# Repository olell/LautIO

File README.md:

# LautIO
Mobile PA-System solution

## Hardware Features

- [x] ESP32 (WiFi + Bluetooth)
- [x] ADAU1701 Digital Signal Processor
- [x] 12V, 5V & 3.3V Power Supply from Battery
- [x] 2x TPA3255-Q1 Amplifier (615W each -> 1260W Amp Power)
- [x] USB Ports to charge mobile phones, etc.
- [x] SD Card socket

## Fancy Rendering

## Third party resources
This git repository contains links or files of the following projects:
* `Bootstrap 5` released under the MIT license. (c) 2021 Twitter
* `Bootswach` released under the MIT license. (c) 2021 Thomas Park
* `jQuery 3.6.0` released under the MIT license. (c) 2021 OpenJS Foundation
* `PlatformIO` released under the Apache 2.0 license. (c) 2021 PlatformIO
* `ESPAsyncTCP` released under the GNU LGPL license. (c) 2021 https://github.com/me-no-dev
* `ESPAsyncWebServer` released under the GNU LGPL license. (c) 2021 https://github.com/me-no-dev
* `SigmaDSP library` released under the GNU LGPL license. (c) 2021 https://github.com/MCUdude
* `ArduinoJson library` released under the MIT license. (c) 2021 Benoît Blanchon

## License
MIT License

Copyright (c) 2021 olel

Permission is hereby granted, free of charge, to any person obtaining a copy
of this software and associated documentation files (the "Software"), to deal
in the Software without restriction, including without limitation the rights
to use, copy, modify, merge, publish, distribute, sublicense, and/or sell
copies of the Software, and to permit persons to whom the Software is
furnished to do so, subject to the following conditions:

The above copyright notice and this permission notice shall be included in all
copies or substantial portions of the Software.

THE SOFTWARE IS PROVIDED "AS IS", WITHOUT WARRANTY OF ANY KIND, EXPRESS OR
IMPLIED, INCLUDING BUT NOT LIMITED TO THE WARRANTIES OF MERCHANTABILITY,
FITNESS FOR A PARTICULAR PURPOSE AND NONINFRINGEMENT. IN NO EVENT SHALL THE
AUTHORS OR COPYRIGHT HOLDERS BE LIABLE FOR ANY CLAIM, DAMAGES OR OTHER
LIABILITY, WHETHER IN AN ACTION OF CONTRACT, TORT OR OTHERWISE, ARISING FROM,
OUT OF OR IN CONNECTION WITH THE SOFTWARE OR THE USE OR OTHER DEALINGS IN THE
SOFTWARE.

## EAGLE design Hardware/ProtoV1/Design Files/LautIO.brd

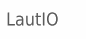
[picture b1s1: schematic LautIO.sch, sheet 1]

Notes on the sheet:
LautIO

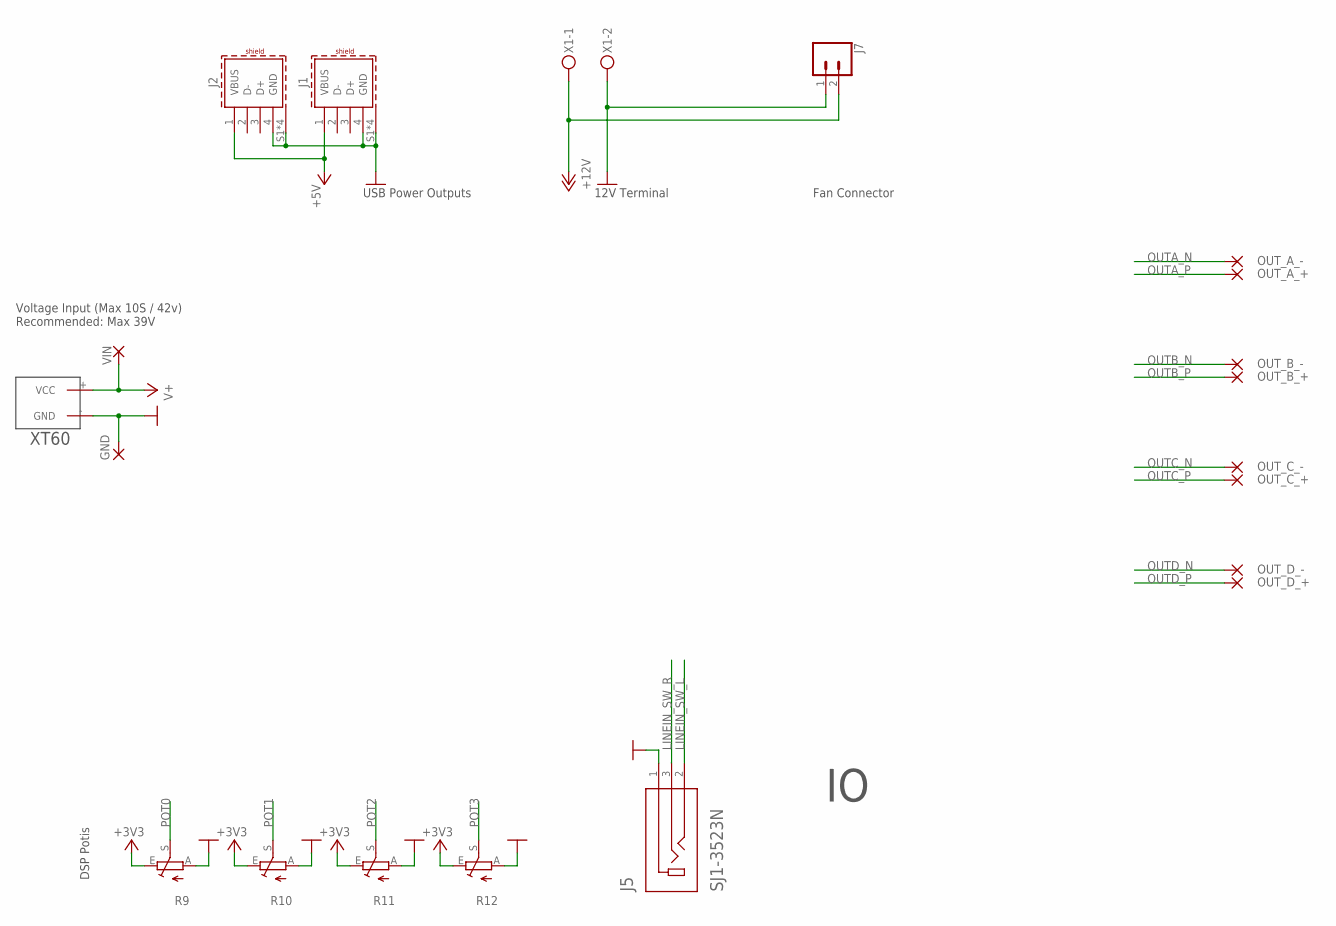
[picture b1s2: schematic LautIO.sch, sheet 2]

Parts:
GND: SMD5; SMD2,54-5,08
J1, J2: 614004134726
J5: SJ1-3523N; CUI_SJ1-3523N
J7: CONN_02; 1X02
OUT_A_+: SMD2; SMD1,27-2,54
OUT_A_-: SMD2; SMD1,27-2,54
OUT_B_+: SMD2; SMD1,27-2,54
OUT_B_-: SMD2; SMD1,27-2,54
OUT_C_+: SMD2; SMD1,27-2,54
OUT_C_-: SMD2; SMD1,27-2,54
OUT_D_+: SMD2; SMD1,27-2,54
OUT_D_-: SMD2; SMD1,27-2,54
R9, R10, R11, R12: TRIM_EU-CIP20C-6MM; CIP20C-6MM
U$1: XT60
VIN: SMD5; SMD2,54-5,08
X1: MKDSN1,5/2-5,08

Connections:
+3V3: R9.E, R10.E, R11.E, R12.E; also elsewhere on the board
+5V: J1.1 (VBUS), J2.1 (VBUS); also elsewhere on the board
+12V: J7.2, X1.1; also elsewhere on the board
GND: GND.1, J1.4 (GND), J1.S1 (SHIELD), J1.S2 (SHIELD), J1.S3 (SHIELD), J1.S4 (SHIELD), J2.4 (GND), J2.S1 (SHIELD), J2.S2 (SHIELD), J2.S3 (SHIELD), J2.S4 (SHIELD), J5.1, J7.1, R9.A, R10.A, R11.A, R12.A, U$1.- (GND), X1.2; also elsewhere on the board
LINEIN_SW_L: J5.2; also elsewhere on the board
LINEIN_SW_R: J5.3; also elsewhere on the board
OUTA_N: OUT_A_-.1; also elsewhere on the board
OUTA_P: OUT_A_+.1; also elsewhere on the board
OUTB_N: OUT_B_-.1; also elsewhere on the board
OUTB_P: OUT_B_+.1; also elsewhere on the board
OUTC_N: OUT_C_-.1; also elsewhere on the board
OUTC_P: OUT_C_+.1; also elsewhere on the board
OUTD_N: OUT_D_-.1; also elsewhere on the board
OUTD_P: OUT_D_+.1; also elsewhere on the board
POT0: R9.S; also elsewhere on the board
POT1: R10.S; also elsewhere on the board
POT2: R11.S; also elsewhere on the board
POT3: R12.S; also elsewhere on the board
V+: U$1.+ (VCC), VIN.1; also elsewhere on the board

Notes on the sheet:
USB Power Outputs
Voltage Input (Max 10S / 42v) Recommended: Max 39V
12V Terminal
DSP Potis
Fan Connector

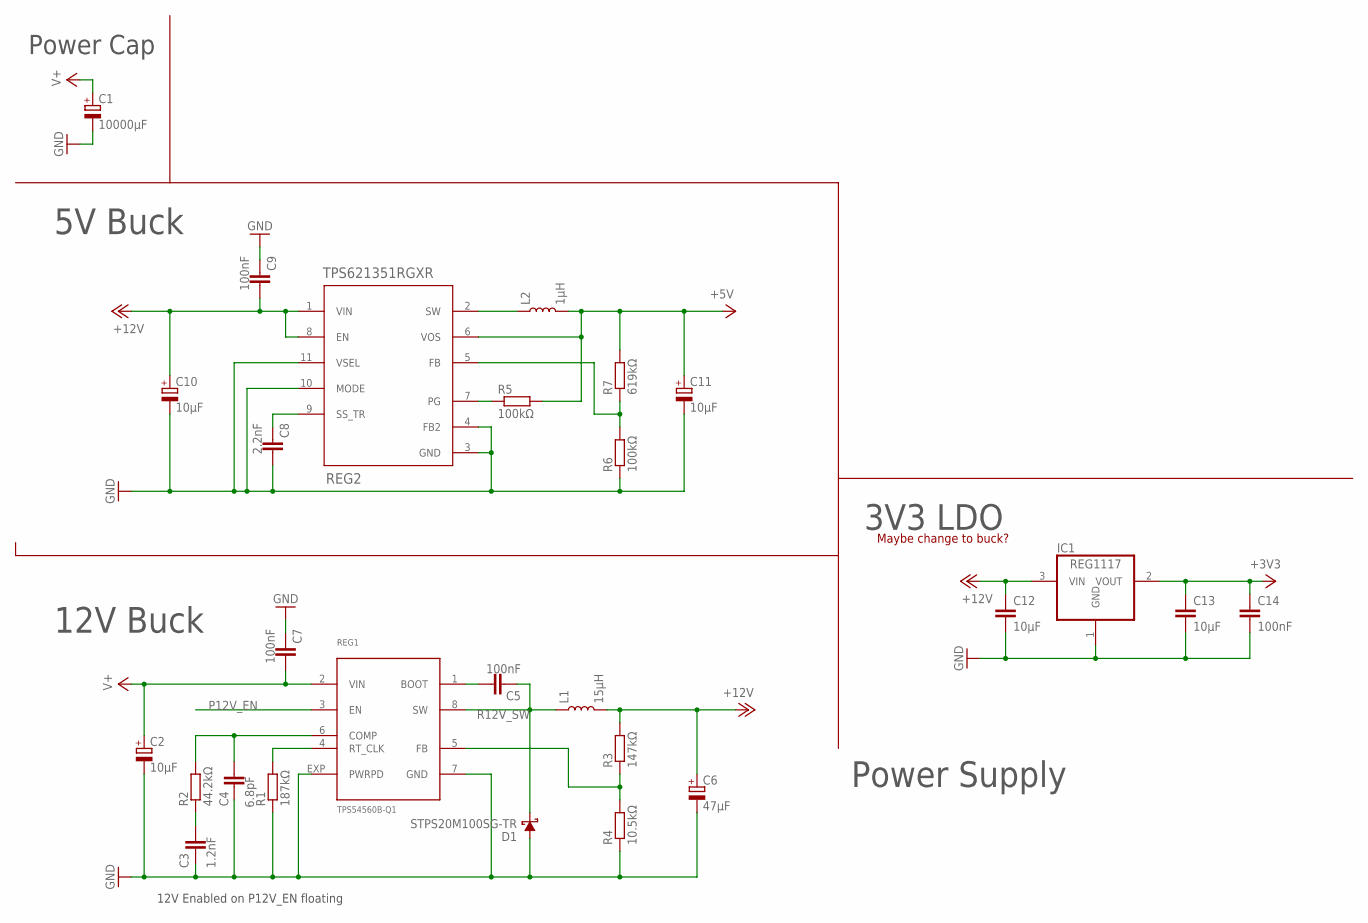
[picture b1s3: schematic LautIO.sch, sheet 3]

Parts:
C1: 10000µF; EB35D
C2, C10, C11: 10µF; 153CLV-0605
C3: 1.2nF; C0603
C4: 6.8pF; C0603
C5, C7, C9, C14: 100nF; C0603
C6: 47µF; 153CLV-0807
C8: 2.2nF; C0603
C12, C13: 10µF; C1206
D1: STPS20M100SG-TR; TO-263/D2PAK
IC1: REG1117; SOT223
L1: 15µH; INDUCTOR_SDR1307
L2: 1µH; INDUCTOR_4X4MM
R1: 187kΩ; R0603
R2: 44.2kΩ; R0603
R3: 147kΩ; R0603
R4: 10.5kΩ; R0603
R5, R6: 100kΩ; R0603
R7: 619kΩ; R0603
REG1: TPS54560B-Q1; HSOP8
REG2: TPS621351RGXR; RGX0011A

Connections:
+3V3: C13.1, C14.1, IC1.2 (VOUT); also elsewhere on the board
+5V: C11.+, L2.P$2 (2), R5.2, R7.2, REG2.6 (VOS); also elsewhere on the board
+12V: C6.+, C9.1, C10.+, C12.1, IC1.3 (VIN), L1.P$2 (2), R3.2, REG2.1 (VIN), REG2.8 (EN); also elsewhere on the board
GND: C1.-, C2.-, C3.2, C4.2, C6.-, C7.2, C8.1, C9.2, C10.-, C11.-, C12.2, C13.2, C14.2, D1.1 (A), D1.3 (A), IC1.1 (GND), R1.1, R4.1, R6.1, REG1.7 (GND), REG1.EXP (PWRPD), REG2.3 (GND), REG2.4 (FB2), REG2.10 (MODE), REG2.11 (VSEL); also elsewhere on the board
unnamed: R1.2, REG1.4 (RT_CLK)
unnamed: C4.1, R2.2, REG1.6 (COMP)
unnamed: C3.1, R2.1
unnamed: C5.1, REG1.1 (BOOT)
unnamed: R6.2, R7.1, REG2.5 (FB)
unnamed: R3.1, R4.2, REG1.5 (FB)
unnamed: L2.P$1 (1), REG2.2 (SW)
unnamed: R5.1, REG2.7 (PG)
unnamed: C8.2, REG2.9 (SS_TR)
P12V_EN: REG1.3 (EN)
R12V_SW: C5.2, D1.2 (C), L1.P$1 (1), REG1.8 (SW)
V+: C1.+, C2.+, C7.1, REG1.2 (VIN); also elsewhere on the board

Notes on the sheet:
Power Supply
Power Cap
12V Enabled on P12V_EN floating
12V Buck
5V Buck
3V3 LDO
Maybe change to buck?

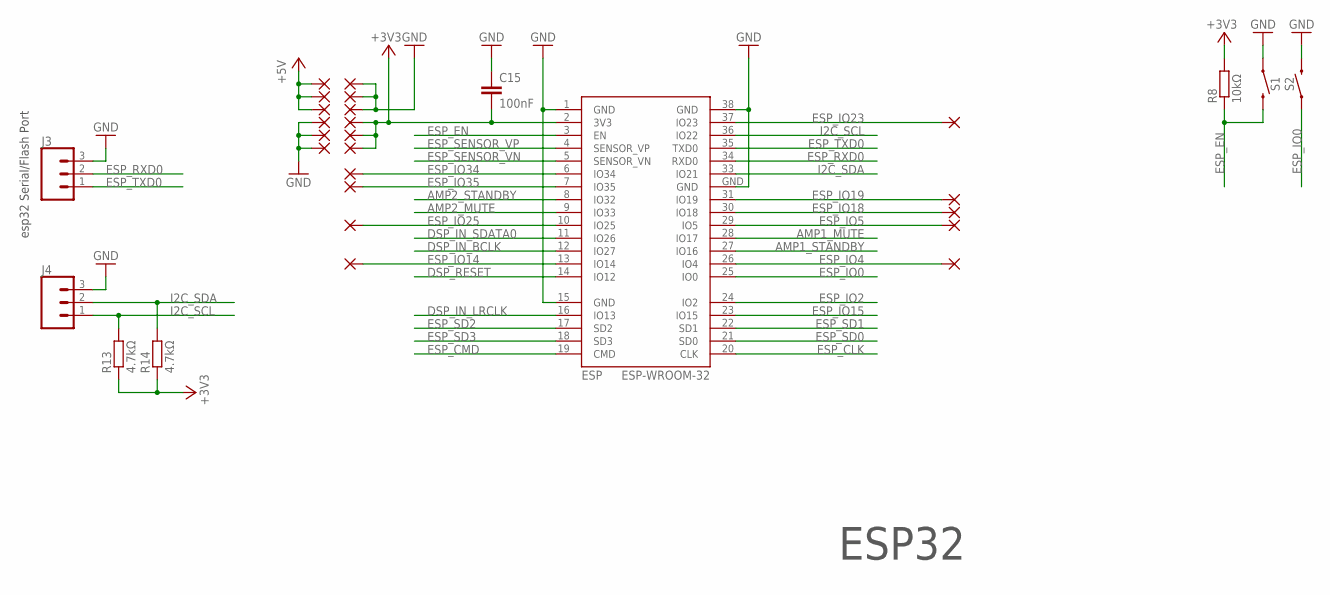
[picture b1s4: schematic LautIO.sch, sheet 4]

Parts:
C15: 100nF; C0603
ESP: ESP-WROOM-32
IO4, IO5, IO14, IO18, IO19, IO23, IO25, IO34, IO35: SMD2; SMD1,27-2,54
J3, J4: 455-1750-1-ND; 1X03
PAD1, PAD2, PAD3, PAD4, PAD5, PAD6, PAD7, PAD8, PAD9, PAD10, PAD11, PAD12: SMD2; SMD1,27-2,54
R8: 10kΩ; R0603
R13, R14: 4.7kΩ; R0603
S1, S2: MOMENTARY-SWITCH-SPST-SMD-6.2MM-TALL; TACTILE_SWITCH_SMD_6.2MM_TALL

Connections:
+3V3: C15.2, ESP.2 (3V3), PAD2.1, PAD4.1, PAD10.1, R8.2, R13.1, R14.1; also elsewhere on the board
+5V: PAD5.1, PAD6.1, PAD7.1; also elsewhere on the board
AMP1_MUTE: ESP.28 (IO17); also elsewhere on the board
AMP1_STANDBY: ESP.27 (IO16); also elsewhere on the board
AMP2_MUTE: ESP.9 (IO33); also elsewhere on the board
AMP2_STANDBY: ESP.8 (IO32); also elsewhere on the board
DSP_IN_BCLK: ESP.12 (IO27); also elsewhere on the board
DSP_IN_LRCLK: ESP.16 (IO13); also elsewhere on the board
DSP_IN_SDATA0: ESP.11 (IO26); also elsewhere on the board
DSP_RESET: ESP.14 (IO12); also elsewhere on the board
ESP_CLK: ESP.20 (CLK)
ESP_CMD: ESP.19 (CMD)
ESP_EN: ESP.3 (EN), R8.1, S1.B2 (2)
ESP_IO0: ESP.25 (IO0), S2.A2 (1)
ESP_IO2: ESP.24 (IO2)
ESP_IO4: ESP.26 (IO4), IO4.1
ESP_IO5: ESP.29 (IO5), IO5.1
ESP_IO14: ESP.13 (IO14), IO14.1
ESP_IO15: ESP.23 (IO15)
ESP_IO18: ESP.30 (IO18), IO18.1
ESP_IO19: ESP.31 (IO19), IO19.1
ESP_IO23: ESP.37 (IO23), IO23.1
ESP_IO25: ESP.10 (IO25), IO25.1
ESP_IO34: ESP.6 (IO34), IO34.1
ESP_IO35: ESP.7 (IO35), IO35.1
ESP_RXD0: ESP.34 (RXD0), J3.2
ESP_SD0: ESP.21 (SD0)
ESP_SD1: ESP.22 (SD1)
ESP_SD2: ESP.17 (SD2)
ESP_SD3: ESP.18 (SD3)
ESP_SENSOR_VN: ESP.5 (SENSOR_VN)
ESP_SENSOR_VP: ESP.4 (SENSOR_VP)
ESP_TXD0: ESP.35 (TXD0), J3.1
GND: C15.1, ESP.1 (GND), ESP.15 (GND), ESP.38 (GND), ESP.GND, J3.3, J4.3, PAD1.1, PAD3.1, PAD8.1, PAD9.1, PAD11.1, PAD12.1, S1.A2 (1), S2.B2 (2); also elsewhere on the board
I2C_SCL: ESP.36 (IO22), J4.1, R13.2; also elsewhere on the board
I2C_SDA: ESP.33 (IO21), J4.2, R14.2; also elsewhere on the board

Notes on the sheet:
ESP32
esp32 Serial/Flash Port

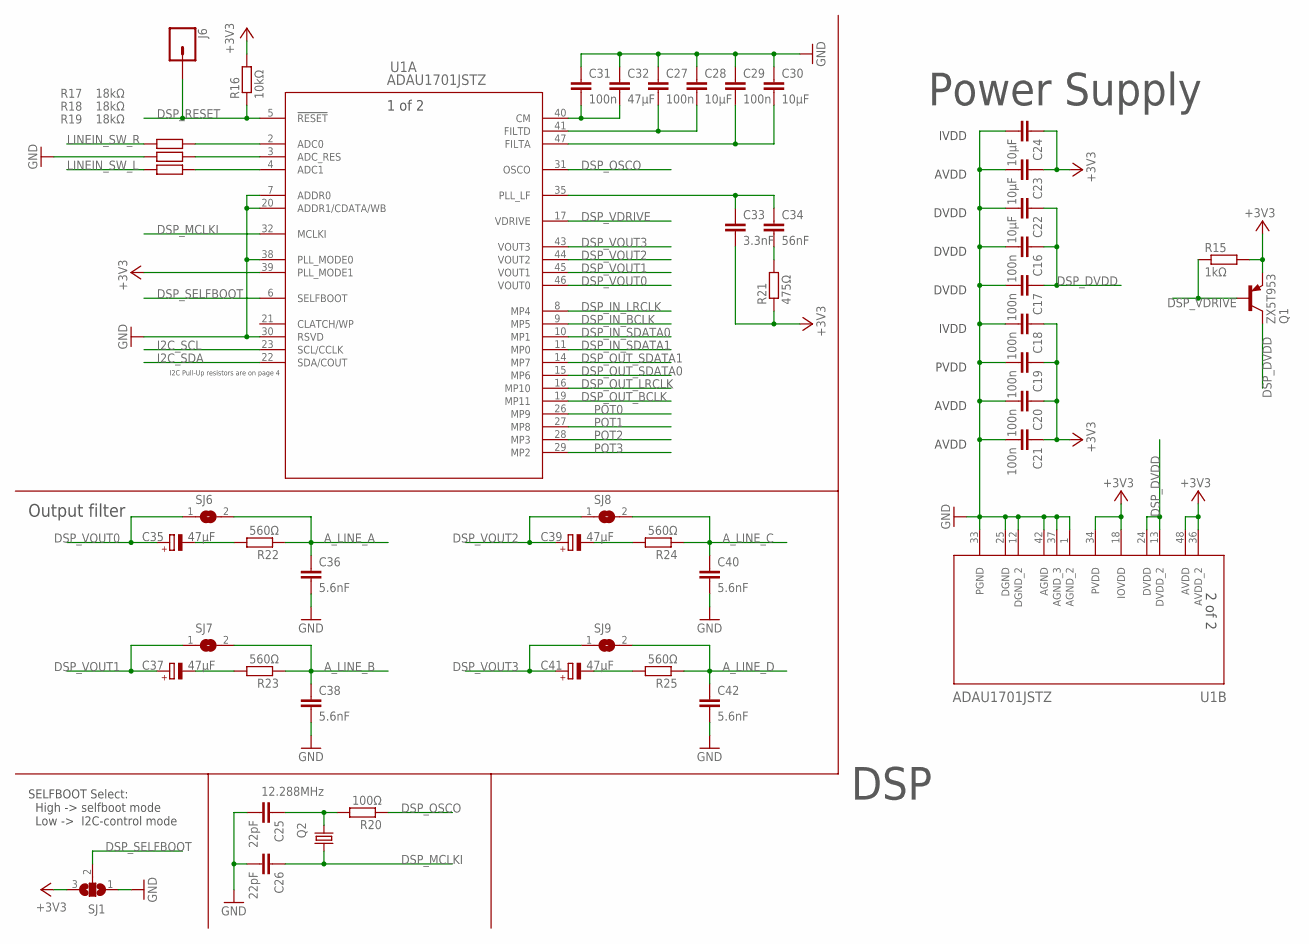
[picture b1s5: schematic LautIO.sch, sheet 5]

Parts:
C16, C17, C18, C19, C20, C21, C27, C29, C31: 100n; C0603
C22, C23, C24, C28, C30: 10µF; C1206K
C25, C26: 22pF; C0603
C32: 47µF; C1206K
C33: 3.3nF; C0603
C34: 56nF; C0603
C35, C37, C39, C41: 47µF; 153CLV-0605
C36, C38, C40, C42: 5.6nF; C0603
J6: CONN_01; 1X01
Q1: ZX5T953; SOT223
Q2: 12.288MHz; CSM-7X-DU
R15: 1kΩ; R0603
R16: 10kΩ; R0603
R17, R18, R19: 18kΩ; R0603
R20: 100Ω; R0603
R21: 475Ω; R0603
R22, R23, R24, R25: 560Ω; R0603
SJ1: SJ2W; SJ_2
SJ6, SJ7, SJ8, SJ9: SJ
U1: ADAU1701JSTZ; ST_48_ADI

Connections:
+3V3: C18.1, C19.1, C20.1, C21.1, C23.1, C24.1, C33.2, Q1.3 (E), R15.2, R16.2, R21.1, SJ1.3, U1.18 (IOVDD), U1.34 (PVDD), U1.36 (AVDD_2), U1.39 (PLL_MODE1), U1.48 (AVDD); also elsewhere on the board
A_LINE_A: C36.1, R22.1, SJ6.2; also elsewhere on the board
A_LINE_B: C38.1, R23.1, SJ7.2; also elsewhere on the board
A_LINE_C: C40.1, R24.1, SJ8.2; also elsewhere on the board
A_LINE_D: C42.1, R25.1, SJ9.2; also elsewhere on the board
DSP_DVDD: C16.1, C17.1, C22.1, Q1.2 (C), Q1.4 (C), U1.13 (DVDD_2), U1.24 (DVDD)
DSP_IN_BCLK: U1.9 (MP5); also elsewhere on the board
DSP_IN_LRCLK: U1.8 (MP4); also elsewhere on the board
DSP_IN_SDATA0: U1.10 (MP1); also elsewhere on the board
DSP_IN_SDATA1: U1.11 (MP0)
DSP_MCLKI: C26.1, Q2.1, U1.32 (MCLKI)
DSP_OSCO: R20.1, U1.31 (OSCO)
DSP_OUT_BCLK: U1.19 (MP11)
DSP_OUT_LRCLK: U1.16 (MP10)
DSP_OUT_SDATA0: U1.15 (MP6)
DSP_OUT_SDATA1: U1.14 (MP7)
DSP_RESET: J6.1, R16.1, U1.5 (!RESET); also elsewhere on the board
DSP_SELFBOOT: SJ1.2, U1.6 (SELFBOOT)
DSP_VDRIVE: Q1.1 (B), R15.1, U1.17 (VDRIVE)
DSP_VOUT0: C35.+, SJ6.1, U1.46 (VOUT0)
DSP_VOUT1: C37.+, SJ7.1, U1.45 (VOUT1)
DSP_VOUT2: C39.+, SJ8.1, U1.44 (VOUT2)
DSP_VOUT3: C41.+, SJ9.1, U1.43 (VOUT3)
GND: C16.2, C17.2, C18.2, C19.2, C20.2, C21.2, C22.2, C23.2, C24.2, C25.2, C26.2, C27.1, C28.1, C29.1, C30.1, C31.1, C32.1, C36.2, C38.2, C40.2, C42.2, R18.2, SJ1.1, U1.1 (AGND_2), U1.7 (ADDR0), U1.12 (DGND_2), U1.20 (ADDR1/CDATA/WB), U1.25 (DGND), U1.30 (RSVD), U1.33 (PGND), U1.37 (AGND_3), U1.38 (PLL_MODE0), U1.42 (AGND); also elsewhere on the board
I2C_SCL: U1.23 (SCL/CCLK); also elsewhere on the board
I2C_SDA: U1.22 (SDA/COUT); also elsewhere on the board
LINEIN_SW_L: R19.2; also elsewhere on the board
LINEIN_SW_R: R17.2; also elsewhere on the board
unnamed: R17.1, U1.2 (ADC0)
unnamed: R18.1, U1.3 (ADC_RES)
unnamed: R19.1, U1.4 (ADC1)
unnamed: C25.1, Q2.2, R20.2
unnamed: C27.2, C28.2, U1.41 (FILTD)
unnamed: C31.2, C32.2, U1.40 (CM)
unnamed: C29.2, C30.2, U1.47 (FILTA)
unnamed: C33.1, C34.1, U1.35 (PLL_LF)
unnamed: C34.2, R21.2
unnamed: C35.-, R22.2
unnamed: C37.-, R23.2
unnamed: C39.-, R24.2
unnamed: C41.-, R25.2
POT0: U1.26 (MP9); also elsewhere on the board
POT1: U1.27 (MP8); also elsewhere on the board
POT2: U1.28 (MP3); also elsewhere on the board
POT3: U1.29 (MP2); also elsewhere on the board

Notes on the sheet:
DSP
Power Supply
AVDD
PVDD
IVDD
DVDD
I2C Pull-Up resistors are on page 4
SELFBOOT Select: High -> selfboot mode Low -> I2C-control mode
Output filter

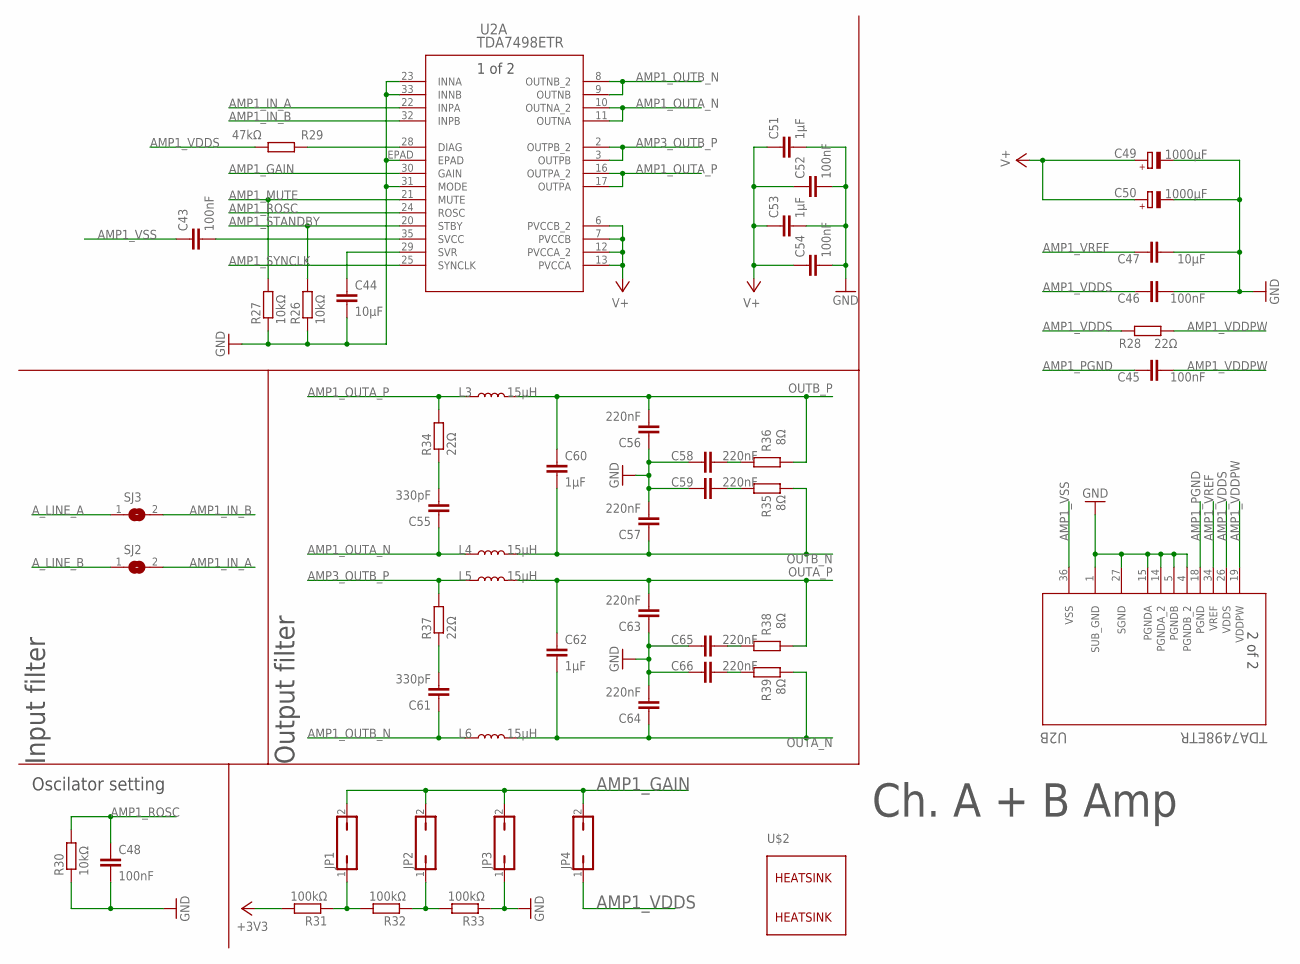
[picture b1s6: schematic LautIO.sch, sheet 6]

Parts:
C43, C45, C46, C48, C52, C54: 100nF; C0603
C44, C47: 10µF; C1206K
C49, C50: 1000µF; E7,5-16
C51, C53: 1µF; C0603
C55, C61: 330pF; C0603
C56, C57, C58, C59, C63, C64, C65, C66: 220nF; C0603
C60, C62: 1µF; C3640
JP1, JP2, JP3, JP4: JP1Q; JP1
L3, L4, L5, L6: 15µH; INDUCTOR_SDR1307
R26, R27, R30: 10kΩ; R0603
R28, R34, R37: 22Ω; R0603
R29: 47kΩ; R0603
R31, R32, R33: 100kΩ; R0603
R35, R36, R38, R39: 8Ω; R0603
SJ2, SJ3: SJ
U2: TDA7498ETR; SSO36_TDA7498ETR_STM
U$2: ATS-CPX030030030

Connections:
+3V3: R31.2; also elsewhere on the board
AMP1_GAIN: JP1.2, JP2.2, JP3.2, JP4.2, U2.30 (GAIN)
AMP1_IN_A: SJ2.2, U2.22 (INPA)
AMP1_IN_B: SJ3.2, U2.32 (INPB)
AMP1_MUTE: R27.2, U2.21 (MUTE); also elsewhere on the board
AMP1_OUTA_N: C55.1, L4.P$1 (1), U2.10 (OUTNA_2), U2.11 (OUTNA)
AMP1_OUTA_P: L3.P$1 (1), R34.2, U2.16 (OUTPA_2), U2.17 (OUTPA)
AMP1_OUTB_N: C61.1, L6.P$1 (1), U2.8 (OUTNB_2), U2.9 (OUTNB)
AMP1_PGND: C45.1, U2.18 (PGND)
AMP1_ROSC: C48.2, R30.2, U2.24 (ROSC)
AMP1_STANDBY: R26.2, U2.20 (STBY); also elsewhere on the board
AMP1_SYNCLK: U2.25 (SYNCLK)
AMP1_VDDPW: C45.2, R28.2, U2.19 (VDDPW)
AMP1_VDDS: C46.1, JP4.1, R28.1, R29.2, U2.26 (VDDS)
AMP1_VREF: C47.1, U2.34 (VREF)
AMP1_VSS: C43.1, U2.36 (VSS)
AMP3_OUTB_P: L5.P$1 (1), R37.2, U2.2 (OUTPB_2), U2.3 (OUTPB)
A_LINE_A: SJ3.1; also elsewhere on the board
A_LINE_B: SJ2.1; also elsewhere on the board
GND: C44.2, C46.2, C47.2, C48.1, C49.-, C50.-, C51.2, C52.2, C53.2, C54.2, C56.1, C57.2, C58.2, C59.2, C63.1, C64.2, C65.2, C66.2, JP3.1, R26.1, R27.1, R30.1, R33.1, U2.1 (SUB_GND), U2.4 (PGNDB_2), U2.5 (PGNDB), U2.14 (PGNDA_2), U2.15 (PGNDA), U2.23 (INNA), U2.27 (SGND), U2.31 (MODE), U2.33 (INNB), U2.EPAD; also elsewhere on the board
unnamed: C43.2, U2.35 (SVCC)
unnamed: C44.1, U2.29 (SVR)
unnamed: R29.1, U2.28 (DIAG)
unnamed: JP1.1, R31.1, R32.2
unnamed: JP2.1, R32.1, R33.2
unnamed: C55.2, R34.1
unnamed: C59.1, R35.2
unnamed: C58.1, R36.2
unnamed: C61.2, R37.1
unnamed: C65.1, R38.2
unnamed: C66.1, R39.2
OUTA_N: C62.2, C64.1, L6.P$2 (2), R39.1; also elsewhere on the board
OUTA_P: C62.1, C63.2, L5.P$2 (2), R38.1; also elsewhere on the board
OUTB_N: C57.1, C60.2, L4.P$2 (2), R35.1; also elsewhere on the board
OUTB_P: C56.2, C60.1, L3.P$2 (2), R36.1; also elsewhere on the board
V+: C49.+, C50.+, C51.1, C52.1, C53.1, C54.1, U2.6 (PVCCB_2), U2.7 (PVCCB), U2.12 (PVCCA_2), U2.13 (PVCCA); also elsewhere on the board

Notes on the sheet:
Ch. A + B Amp
Oscilator setting
Input filter
Output filter

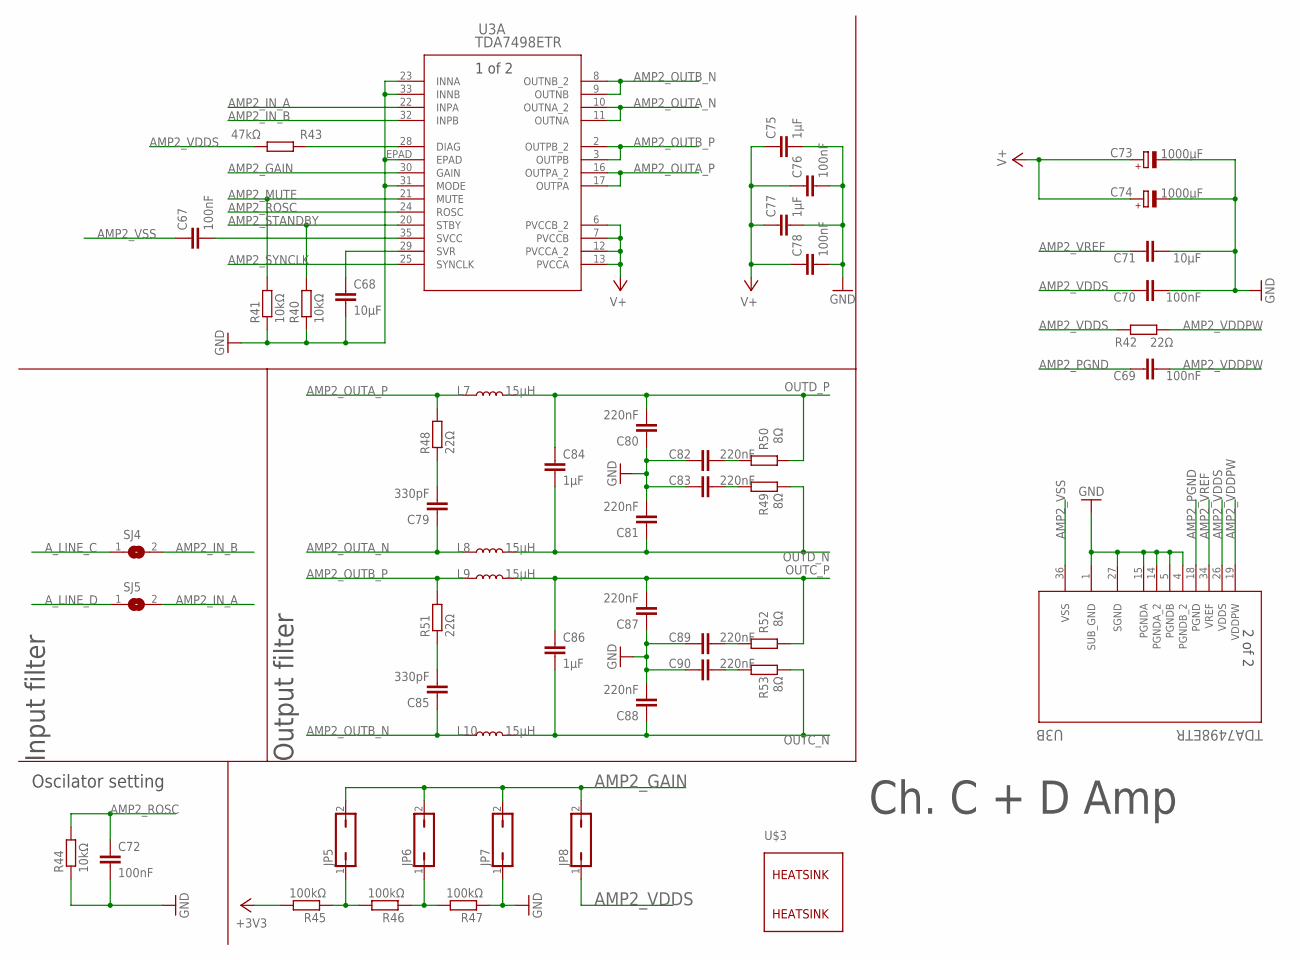
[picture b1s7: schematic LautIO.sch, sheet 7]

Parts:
C67, C69, C70, C72, C76, C78: 100nF; C0603
C68, C71: 10µF; C1206K
C73, C74: 1000µF; E7,5-16
C75, C77: 1µF; C0603
C79, C85: 330pF; C0603
C80, C81, C82, C83, C87, C88, C89, C90: 220nF; C0603
C84, C86: 1µF; C3640
JP5, JP6, JP7, JP8: JP1Q; JP1
L7, L8, L9, L10: 15µH; INDUCTOR_SDR1307
R40, R41, R44: 10kΩ; R0603
R42, R48, R51: 22Ω; R0603
R43: 47kΩ; R0603
R45, R46, R47: 100kΩ; R0603
R49, R50, R52, R53: 8Ω; R0603
SJ4, SJ5: SJ
U3: TDA7498ETR; SSO36_TDA7498ETR_STM
U$3: ATS-CPX030030030

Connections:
+3V3: R45.2; also elsewhere on the board
AMP2_GAIN: JP5.2, JP6.2, JP7.2, JP8.2, U3.30 (GAIN)
AMP2_IN_A: SJ5.2, U3.22 (INPA)
AMP2_IN_B: SJ4.2, U3.32 (INPB)
AMP2_MUTE: R41.2, U3.21 (MUTE); also elsewhere on the board
AMP2_OUTA_N: C79.1, L8.P$1 (1), U3.10 (OUTNA_2), U3.11 (OUTNA)
AMP2_OUTA_P: L7.P$1 (1), R48.2, U3.16 (OUTPA_2), U3.17 (OUTPA)
AMP2_OUTB_N: C85.1, L10.P$1 (1), U3.8 (OUTNB_2), U3.9 (OUTNB)
AMP2_OUTB_P: L9.P$1 (1), R51.2, U3.2 (OUTPB_2), U3.3 (OUTPB)
AMP2_PGND: C69.1, U3.18 (PGND)
AMP2_ROSC: C72.2, R44.2, U3.24 (ROSC)
AMP2_STANDBY: R40.2, U3.20 (STBY); also elsewhere on the board
AMP2_SYNCLK: U3.25 (SYNCLK)
AMP2_VDDPW: C69.2, R42.2, U3.19 (VDDPW)
AMP2_VDDS: C70.1, JP8.1, R42.1, R43.2, U3.26 (VDDS)
AMP2_VREF: C71.1, U3.34 (VREF)
AMP2_VSS: C67.1, U3.36 (VSS)
A_LINE_C: SJ4.1; also elsewhere on the board
A_LINE_D: SJ5.1; also elsewhere on the board
GND: C68.2, C70.2, C71.2, C72.1, C73.-, C74.-, C75.2, C76.2, C77.2, C78.2, C80.1, C81.2, C82.2, C83.2, C87.1, C88.2, C89.2, C90.2, JP7.1, R40.1, R41.1, R44.1, R47.1, U3.1 (SUB_GND), U3.4 (PGNDB_2), U3.5 (PGNDB), U3.14 (PGNDA_2), U3.15 (PGNDA), U3.23 (INNA), U3.27 (SGND), U3.31 (MODE), U3.33 (INNB), U3.EPAD; also elsewhere on the board
unnamed: C67.2, U3.35 (SVCC)
unnamed: C68.1, U3.29 (SVR)
unnamed: R43.1, U3.28 (DIAG)
unnamed: JP5.1, R45.1, R46.2
unnamed: JP6.1, R46.1, R47.2
unnamed: C79.2, R48.1
unnamed: C83.1, R49.2
unnamed: C82.1, R50.2
unnamed: C85.2, R51.1
unnamed: C89.1, R52.2
unnamed: C90.1, R53.2
OUTC_N: C86.2, C88.1, L10.P$2 (2), R53.1; also elsewhere on the board
OUTC_P: C86.1, C87.2, L9.P$2 (2), R52.1; also elsewhere on the board
OUTD_N: C81.1, C84.2, L8.P$2 (2), R49.1; also elsewhere on the board
OUTD_P: C80.2, C84.1, L7.P$2 (2), R50.1; also elsewhere on the board
V+: C73.+, C74.+, C75.1, C76.1, C77.1, C78.1, U3.6 (PVCCB_2), U3.7 (PVCCB), U3.12 (PVCCA_2), U3.13 (PVCCA); also elsewhere on the board

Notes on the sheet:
Ch. C + D Amp
Oscilator setting
Input filter
Output filter

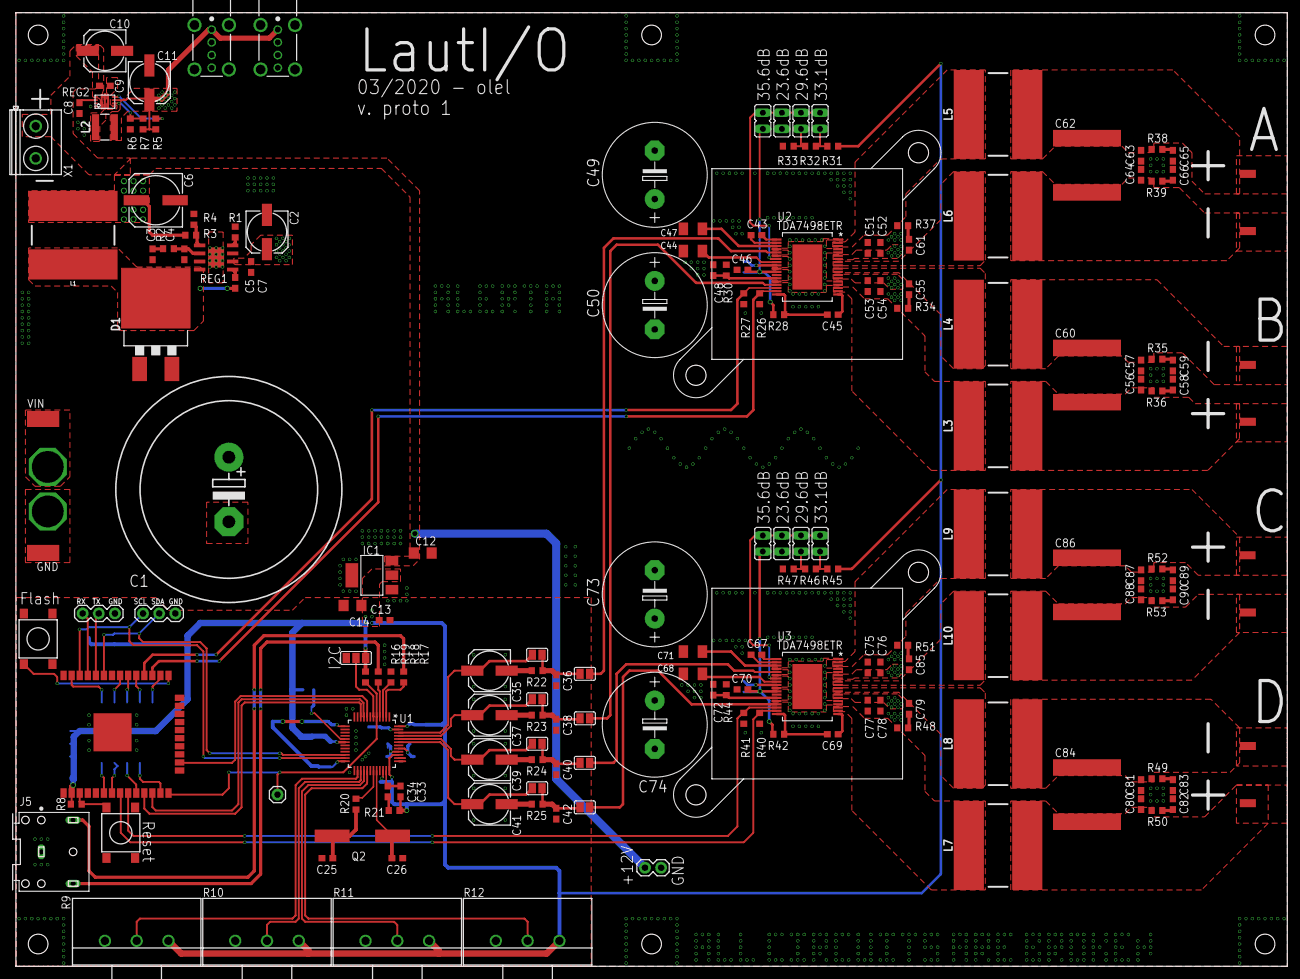
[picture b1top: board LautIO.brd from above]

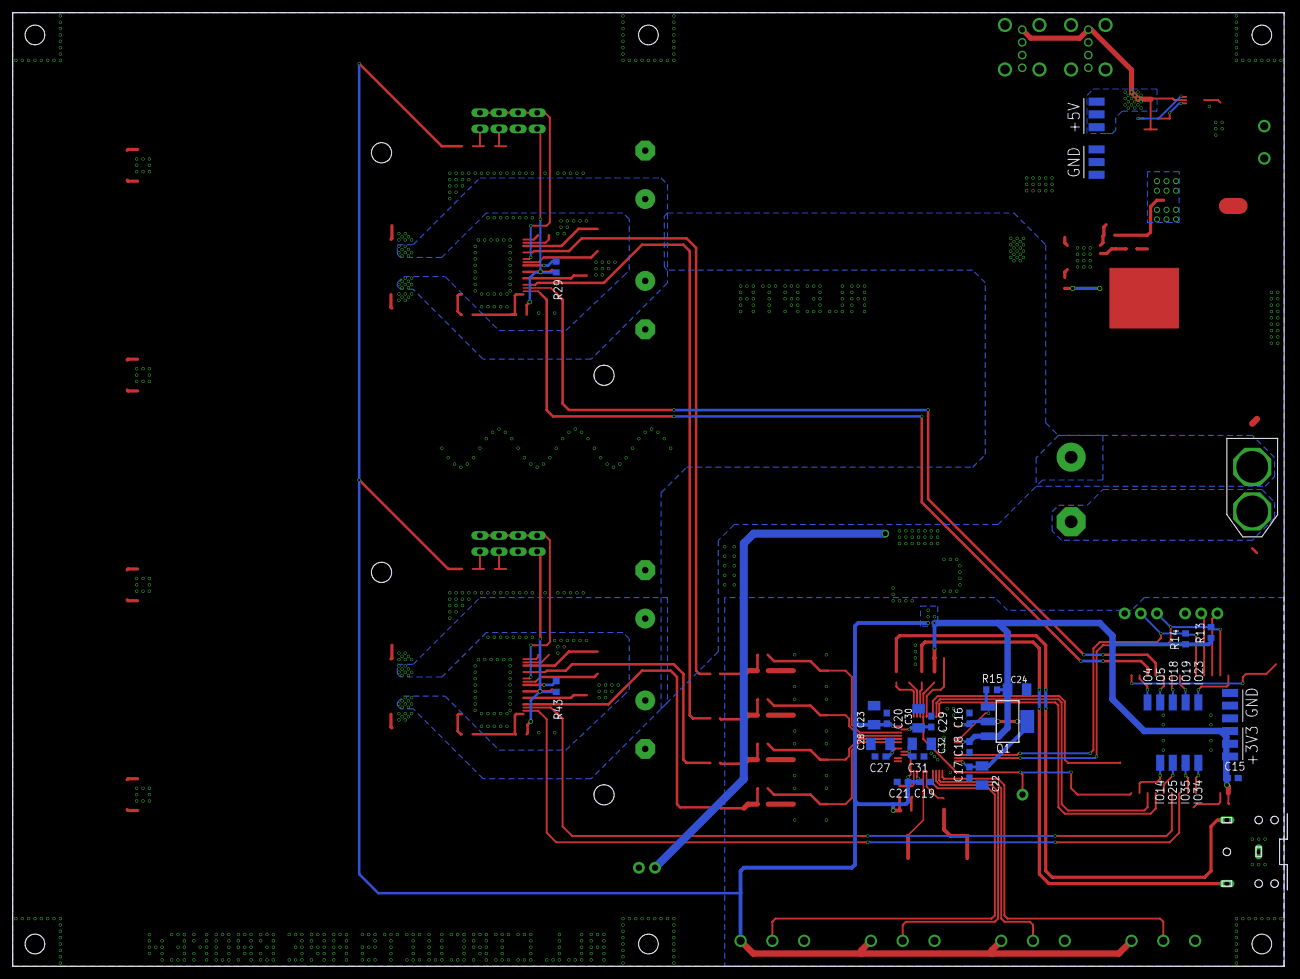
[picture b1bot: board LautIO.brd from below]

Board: 2 copper layers, 200.5 x 150.0 mm, 224 parts (44 on the bottom side), 126 nets.

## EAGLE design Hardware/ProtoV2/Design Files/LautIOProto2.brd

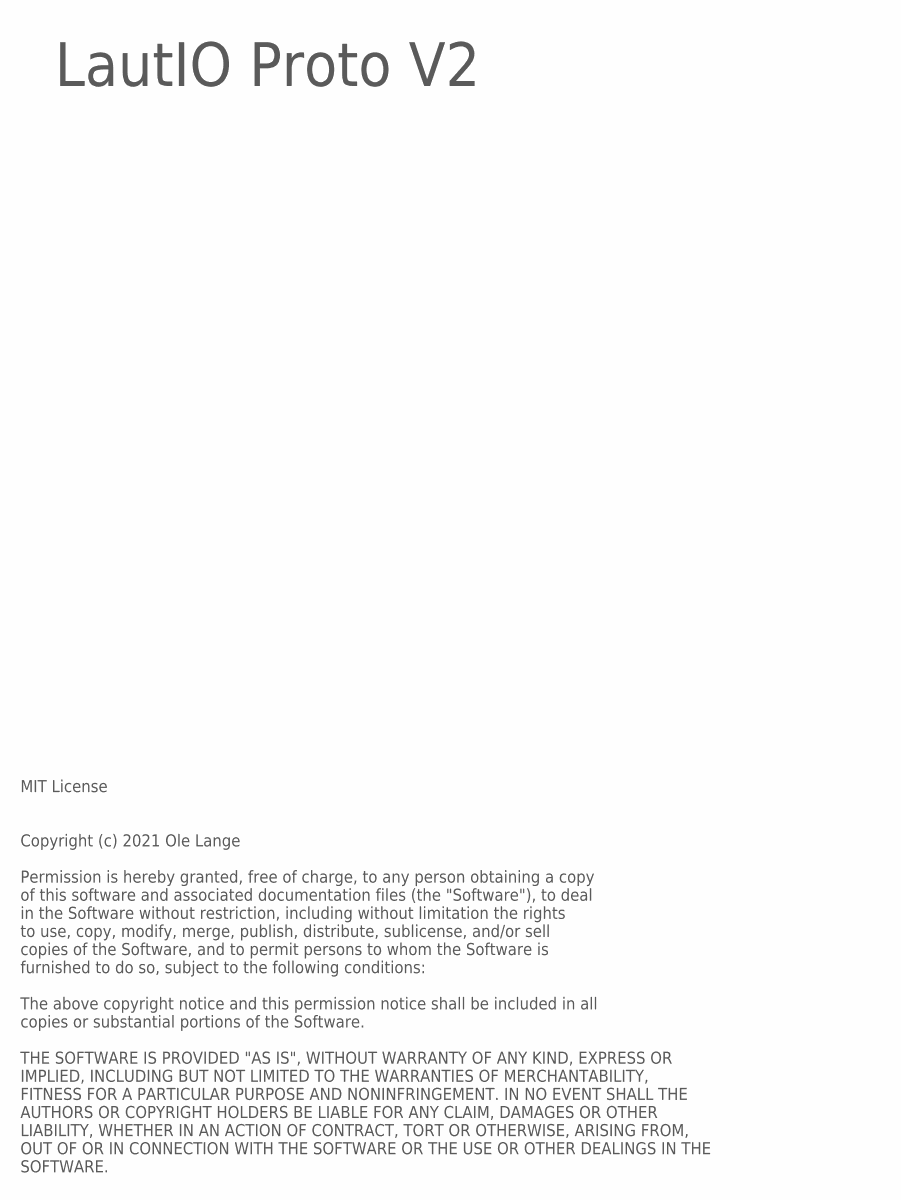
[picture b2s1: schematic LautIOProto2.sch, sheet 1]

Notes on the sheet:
LautIO Proto V2
MIT License Copyright (c) 2021 Ole Lange Permission is hereby granted, free of charge, to any person obtaining a copy of this software and associated documentation files (the "Software"), to deal in the Software without restriction, including without limitation the rights to use, copy, modify, merg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

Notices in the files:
parts and their libraries:
o163744v244+Eagle_WR-USB+: Copyright: Würth Elektronik
olelib: COPYRIGHT: Copyright (C) 2018 Accelerated Designs. All rights reserved
SparkFun-Coils: Licensing: Creative Commons ShareAlike 4.0 International - https://creativecommons.org/licenses/by-sa/4.0
